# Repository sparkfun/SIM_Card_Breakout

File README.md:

Breakout Board for SIM Cards
============================

[
*Breakout Board for SIM Cards (BOB-00573)*](https://www.sparkfun.com/products/573)

8-pin breakout for the SIM socket allowing direct access to SIM communication.

Repository Contents
-------------------

* **/Hardware** - All Eagle design files (.brd, .sch, .STL)
* **/Production** - Test bed files and production panel files

License Information
-------------------
The hardware is released under [Creative Commons ShareAlike 4.0 International](https://creativecommons.org/licenses/by-sa/4.0/).

Distributed as-is; no warranty is given.

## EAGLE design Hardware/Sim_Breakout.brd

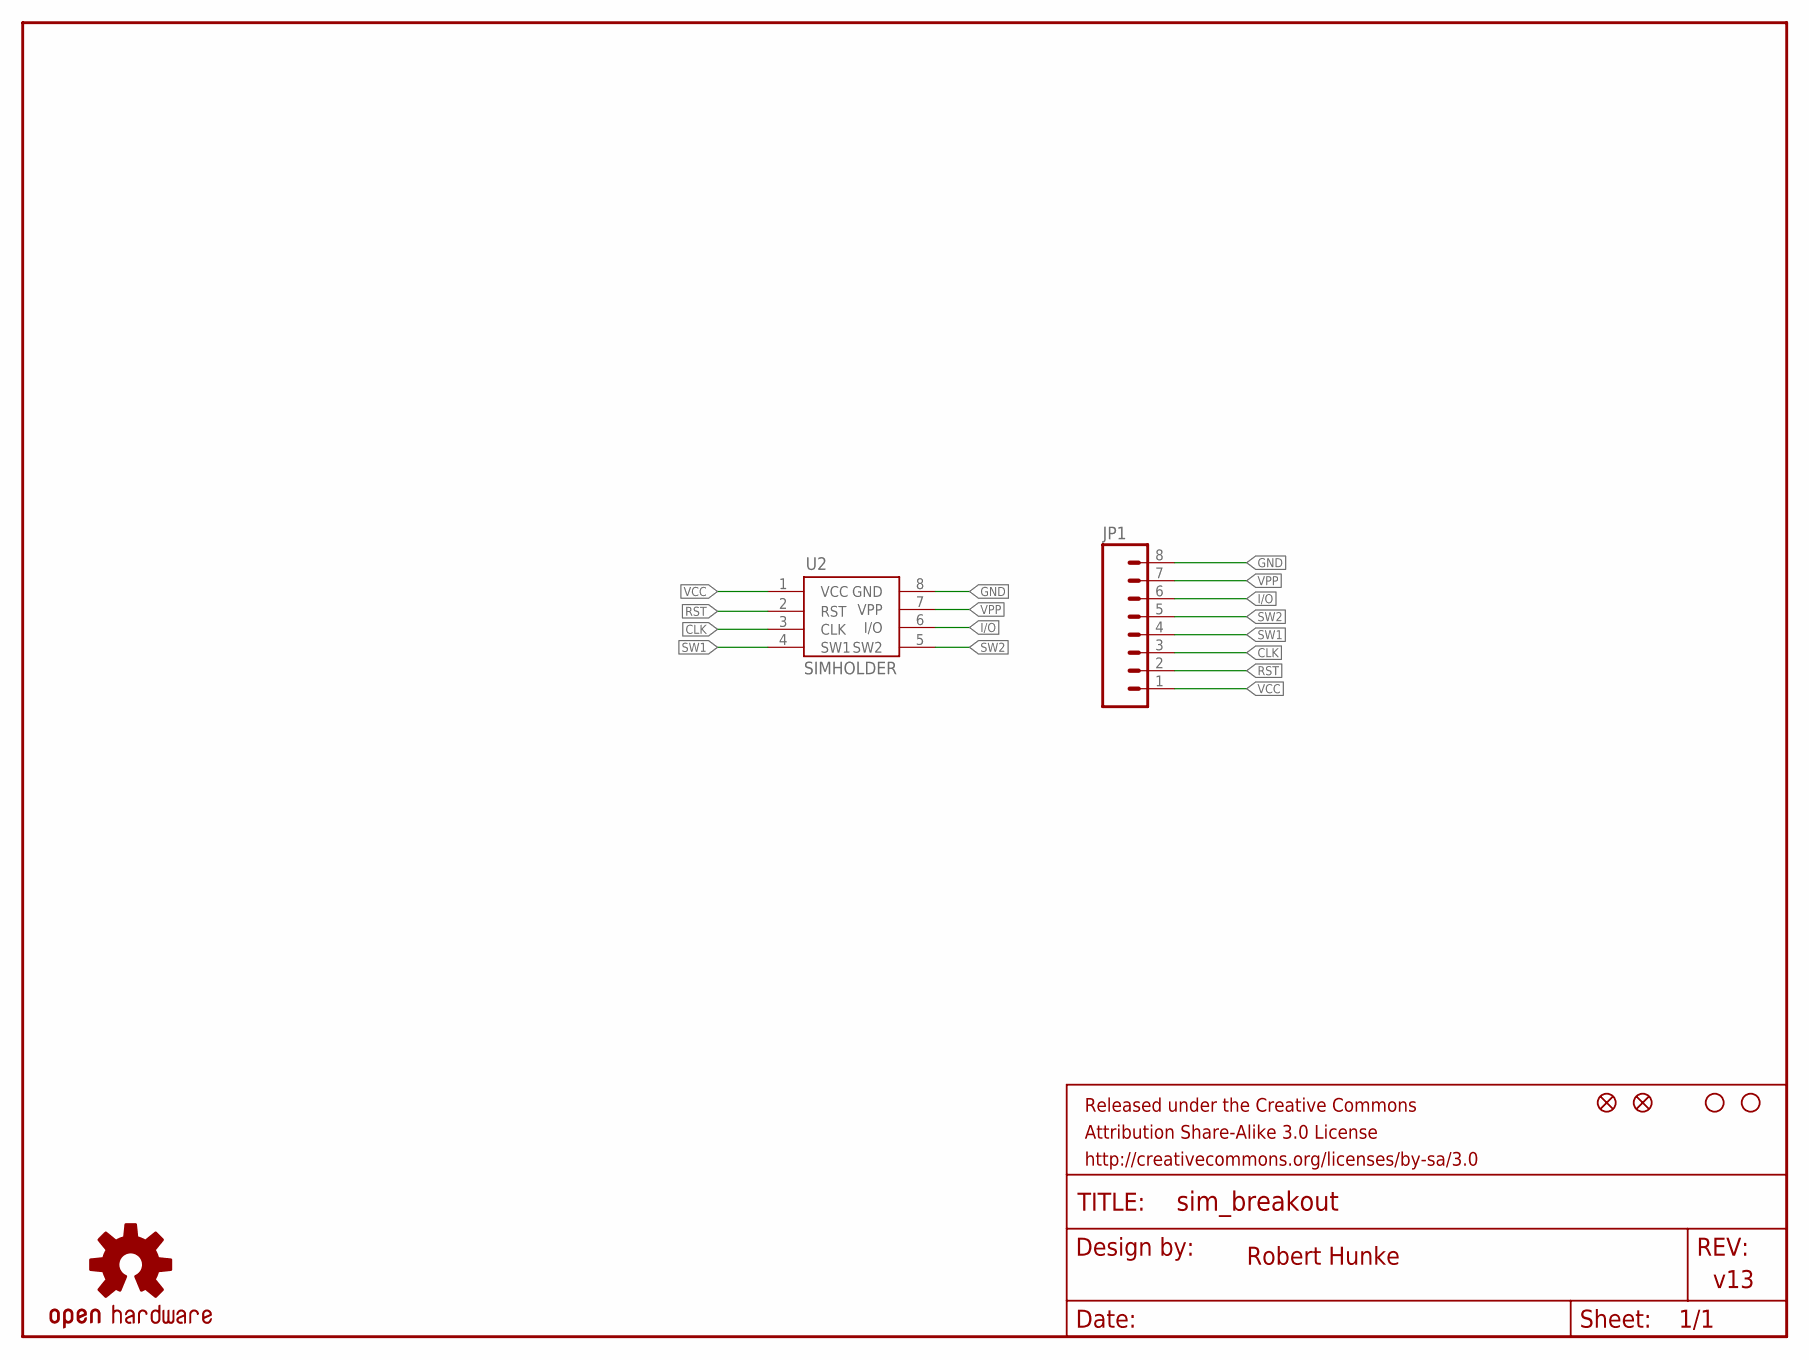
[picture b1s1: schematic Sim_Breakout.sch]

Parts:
FID1, FID2: FIDUCIALUFIDUCIAL; MICRO-FIDUCIAL
FRAME2: FRAME-LETTER; CREATIVE_COMMONS
JP1: M08; 1X08
LOGO1: OSHW-LOGOS; OSHW-LOGO-S
STANDOFF1, STANDOFF2: STAND-OFF
U2: SIMHOLDER; SIMHOLDER2

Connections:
CLK: JP1.3, U2.3 (CLK)
GND: JP1.8, U2.8 (GND)
I/O: JP1.6, U2.6 (I/O)
RST: JP1.2, U2.2 (RST)
SW1: JP1.4, U2.4 (SW1)
SW2: JP1.5, U2.5 (SW2)
VCC: JP1.1, U2.1 (VCC)
VPP: JP1.7, U2.7 (VPP)

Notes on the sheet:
Robert Hunke
v13

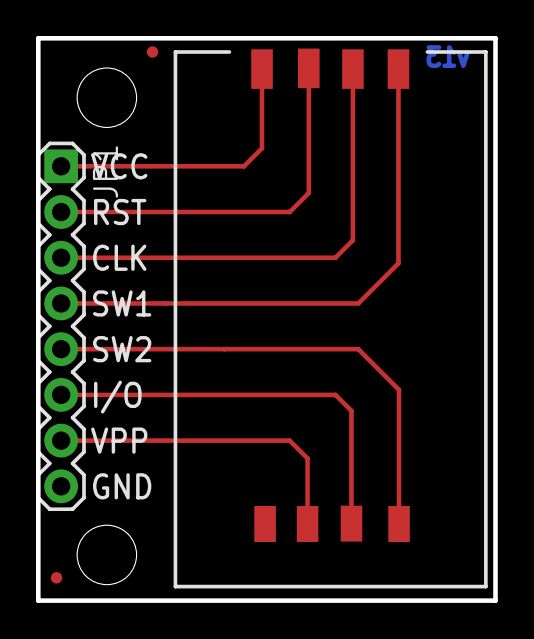
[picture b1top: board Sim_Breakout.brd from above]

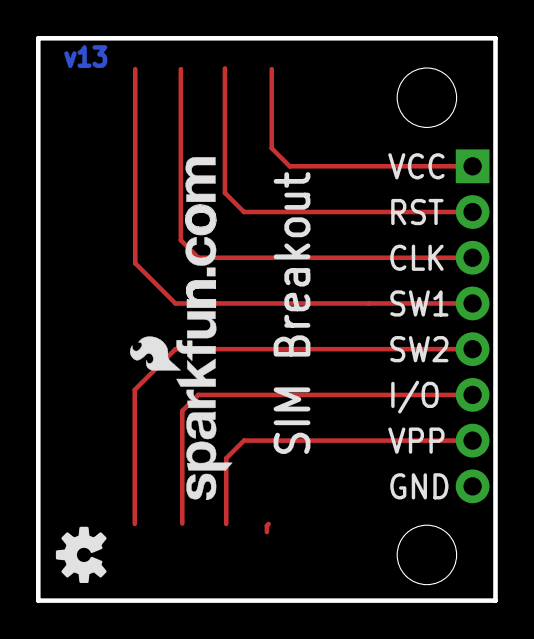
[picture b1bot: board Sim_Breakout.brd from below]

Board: 2 copper layers, 25.4 x 31.2 mm, 9 parts (2 on the bottom side), 8 nets.

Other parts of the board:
U$1: SFE-NEW-WEBLOGO

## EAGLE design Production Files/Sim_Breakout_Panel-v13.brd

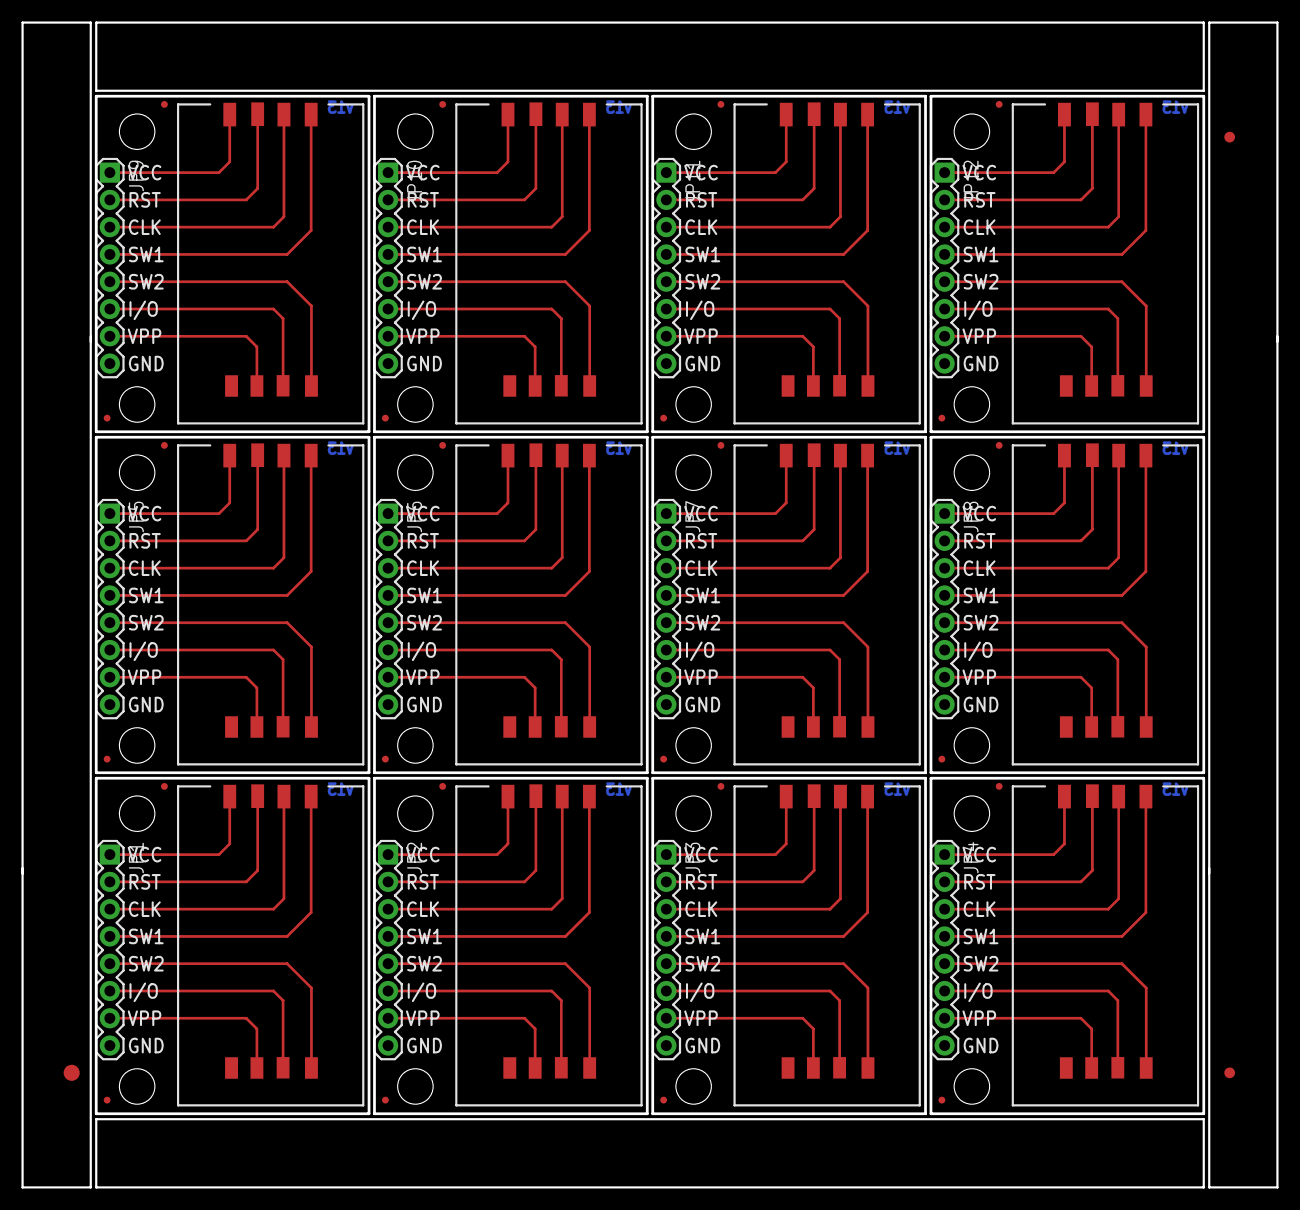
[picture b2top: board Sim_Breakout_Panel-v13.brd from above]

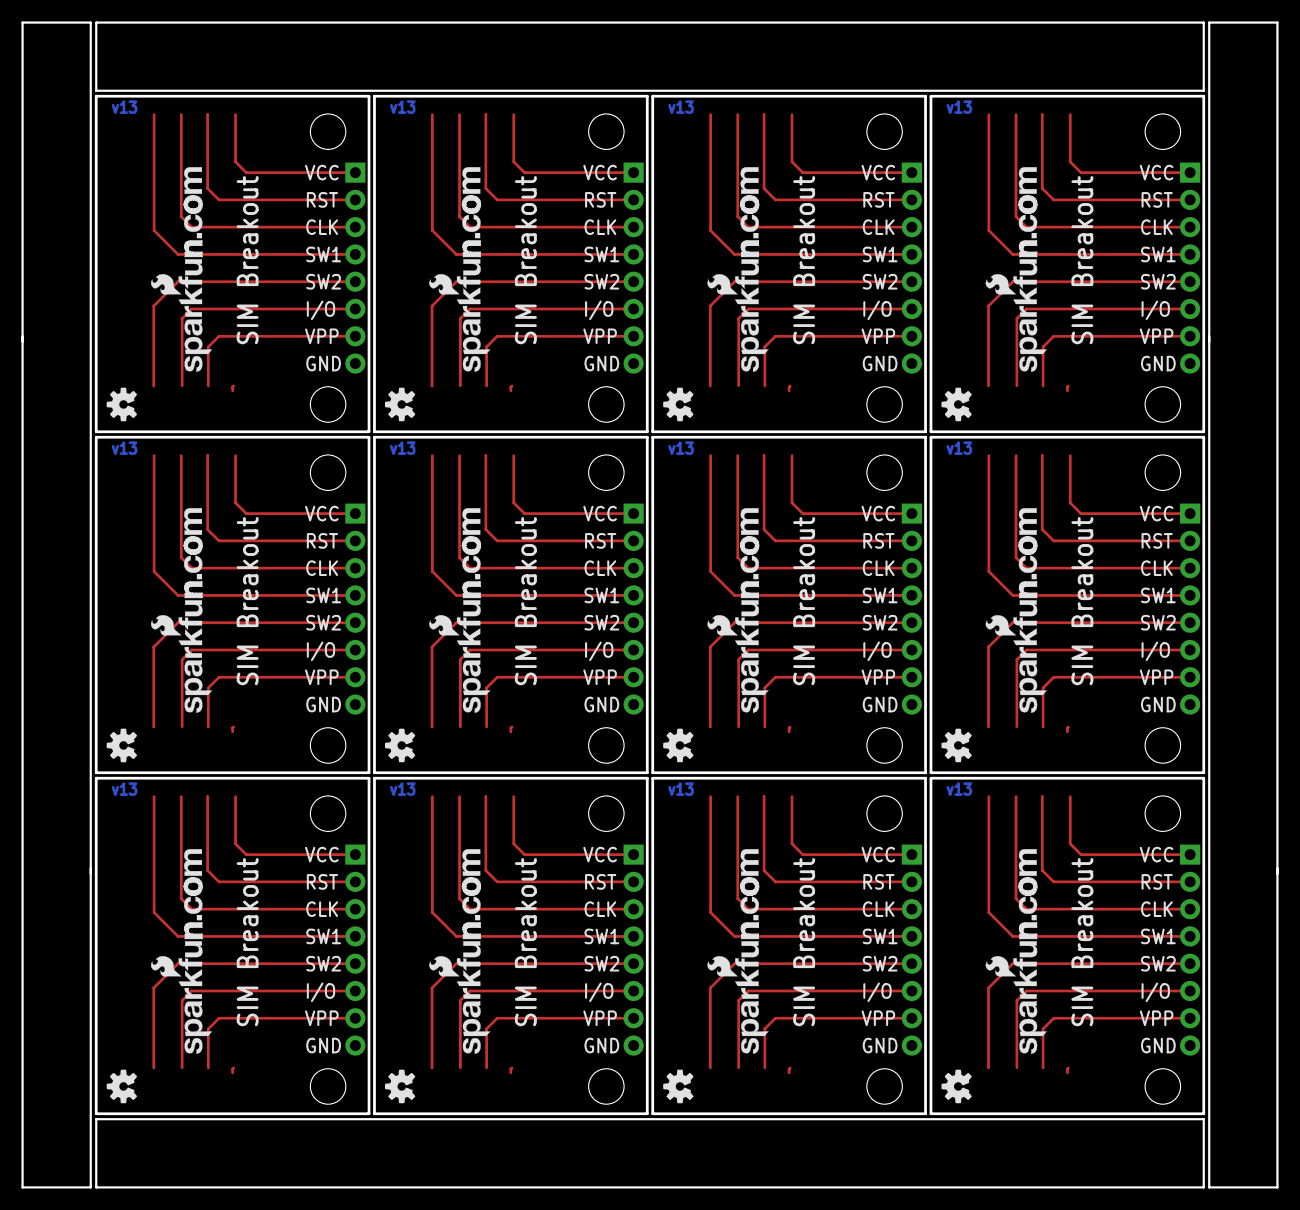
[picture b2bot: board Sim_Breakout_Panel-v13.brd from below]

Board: 2 copper layers, 116.8 x 108.4 mm, 99 parts (24 on the bottom side), 96 nets.

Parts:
E$1: FIDUCIAL-1.5X3
E$4, E$5: FIDUCIAL-1X2
FID1, FID2, FID3, FID4, FID5, FID6, FID7, FID8, FID9, FID10, FID11, FID12, FID13, FID14, FID15, FID16, FID17, FID18, FID19, FID20, FID21, FID22, FID23, FID24: FIDUCIALUFIDUCIAL; MICRO-FIDUCIAL
JP1, JP2, JP3, JP4, JP5, JP6, JP7, JP8, JP9, JP10, JP11, JP12: 1X08
LOGO1, LOGO2, LOGO3, LOGO4, LOGO5, LOGO6, LOGO7, LOGO8, LOGO9, LOGO10, LOGO11, LOGO12: OSHW-LOGOS; OSHW-LOGO-S
STANDOFF1, STANDOFF2, STANDOFF3, STANDOFF4, STANDOFF5, STANDOFF6, STANDOFF7, STANDOFF8, STANDOFF9, STANDOFF10, STANDOFF11, STANDOFF12, STANDOFF13, STANDOFF14, STANDOFF15, STANDOFF16, STANDOFF17, STANDOFF18, STANDOFF19, STANDOFF20, STANDOFF21, STANDOFF22, STANDOFF23, STANDOFF24: STAND-OFF
U1, U2, U3, U4, U5, U6, U7, U8, U9, U10, U11, U12: SIMHOLDER; SIMHOLDER2
U$1, U$2, U$3, U$4, U$5, U$6, U$7, U$8, U$9, U$10, U$11, U$12: SFE-NEW-WEBLOGO

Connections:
CLK: JP1.3, U2.3
CLK1: JP2.3, U1.3
CLK2: JP3.3, U3.3
CLK3: JP4.3, U4.3
CLK4: JP5.3, U5.3
CLK5: JP6.3, U6.3
CLK6: JP7.3, U7.3
CLK7: JP8.3, U8.3
CLK8: JP9.3, U9.3
CLK9: JP10.3, U10.3
CLK10: JP11.3, U11.3
CLK11: JP12.3, U12.3
GND: JP1.8, U2.8
GND1: JP2.8, U1.8
GND2: JP3.8, U3.8
GND3: JP4.8, U4.8
GND4: JP5.8, U5.8
GND5: JP6.8, U6.8
GND6: JP7.8, U7.8
GND7: JP8.8, U8.8
GND8: JP9.8, U9.8
GND9: JP10.8, U10.8
GND10: JP11.8, U11.8
GND11: JP12.8, U12.8
I/O: JP1.6, U2.6
I/O1: JP2.6, U1.6
I/O2: JP3.6, U3.6
I/O3: JP4.6, U4.6
I/O4: JP5.6, U5.6
I/O5: JP6.6, U6.6
I/O6: JP7.6, U7.6
I/O7: JP8.6, U8.6
I/O8: JP9.6, U9.6
I/O9: JP10.6, U10.6
I/O10: JP11.6, U11.6
I/O11: JP12.6, U12.6
RST: JP1.2, U2.2
RST1: JP2.2, U1.2
RST2: JP3.2, U3.2
RST3: JP4.2, U4.2
RST4: JP5.2, U5.2
RST5: JP6.2, U6.2
RST6: JP7.2, U7.2
RST7: JP8.2, U8.2
RST8: JP9.2, U9.2
RST9: JP10.2, U10.2
RST10: JP11.2, U11.2
RST11: JP12.2, U12.2
SW1: JP1.4, U2.4
SW2: JP1.5, U2.5
SW3: JP2.4, U1.4
SW4: JP2.5, U1.5
SW5: JP3.4, U3.4
SW6: JP3.5, U3.5
SW7: JP4.4, U4.4
SW8: JP4.5, U4.5
SW9: JP5.4, U5.4
SW10: JP5.5, U5.5
SW11: JP6.4, U6.4
SW12: JP6.5, U6.5
SW13: JP7.4, U7.4
SW14: JP7.5, U7.5
SW15: JP8.4, U8.4
SW16: JP8.5, U8.5
SW17: JP9.4, U9.4
SW18: JP9.5, U9.5
SW19: JP10.4, U10.4
SW20: JP10.5, U10.5
SW21: JP11.4, U11.4
SW22: JP11.5, U11.5
SW23: JP12.4, U12.4
SW24: JP12.5, U12.5
VCC: JP1.1, U2.1
VCC1: JP2.1, U1.1
VCC2: JP3.1, U3.1
VCC3: JP4.1, U4.1
VCC4: JP5.1, U5.1
VCC5: JP6.1, U6.1
VCC6: JP7.1, U7.1
VCC7: JP8.1, U8.1
VCC8: JP9.1, U9.1
VCC9: JP10.1, U10.1
VCC10: JP11.1, U11.1
VCC11: JP12.1, U12.1
VPP: JP1.7, U2.7
VPP1: JP2.7, U1.7
VPP2: JP3.7, U3.7
VPP3: JP4.7, U4.7
VPP4: JP5.7, U5.7
VPP5: JP6.7, U6.7
VPP6: JP7.7, U7.7
VPP7: JP8.7, U8.7
VPP8: JP9.7, U9.7
VPP9: JP10.7, U10.7
VPP10: JP11.7, U11.7
VPP11: JP12.7, U12.7

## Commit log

2014-01-14 Updated board to v13
    1. Rerouted Traces
    2. Increased isolate to .01
    3. added local fiducials
    4. added mounting holes
    5. converted date code to rev code
2014-01-14 Aesthetic changes
    1. Updated net labels to flags.
    2.) Added OSHW logo to bottom silk.
    3.) Added SFE logo to bottom silk.
2014-01-14 created panel
2014-02-06 Updating README

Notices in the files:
parts and their libraries:
SparkFun-Electromechanical: Licensing: CC v3.0 Share-Alike You are welcome to use this library for commercial purposes.
SparkFun-Aesthetics: Released under the Creative Commons Attribution Share-Alike 3.0 License
SparkFun-Aesthetics: http://creativecommons.org/licenses/by-sa/3.0
